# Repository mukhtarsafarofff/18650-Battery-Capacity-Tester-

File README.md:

(ENG)  Nowadays it is difficult to know the capacity retained in 18650 batteries and when we are buying , it is really difficult to distinguish between a real and fake battery .The whole schematic is divided into to followings sections:
1. Constant Current Load Circuit
2. Battery Voltage Measurement Circuit
3. User Interface Circuit
4. Buzzer Circuit

The power supply circuit consists of a DC Jack ( 7-9V) and two filter capacitors C1 and C2. The power output (Vin) is connected to the Arduino pin Vin. Here I am using the Arduino on-board voltage regulator to step down the voltage to 5V.
The main component of constant current load circuit is LM358 IC.LM358 is a dual amplifier in a single package.
This op-amp, R3, and the MOSFET build a constant current load circuit. When we set the voltage on the non-inverting input pin, the op-amp turns on the MOSFET and tries to get the same voltage across the R3. The Voltage appears due to the ohms law, as current flows through the resistor a voltage drop must appear. So I can control the current through the load resistor (R4) by changing the PWM signal pulse width.
The battery voltage is measured by the Arduino analog input pin A0. Two capacitors C1 and C2 are used to filter out the noises coming from the constant current load circuit which can degrade the ADC conversion performance.The user interface circuit consists of two push buttons and a 0.96" I2C OLED display. The Up and Down push-button is to increase or decrease the PWM pulse width. R3 and R4 are pull-up resistors for the Up and Down push-buttons. C7 and C8 are used to debounce the push buttons. The third push-button (RST) is used for resetting the Arduino.The buzzer circuit is used to alert the starting and end of the test. A 5V buzzer is hooked to Arduino digital pin D9.The theory is based on the voltage comparison of the inverting (pin-2) and the non-inverting (pin-3) inputs of the OpAmp.When I set the voltage applied to the non-inverting input by adjusting the PWM signal, the output of the opamp opens the gate of MOSFET. As the MOSFET turn-on, the current runs through R1, it creates a voltage drop, which provides negative feedback to OpAmp. It controls the MOSFET in such a way that the voltages at its inverting and non-inverting inputs are equal.The PWM signal from the Arduino is filtered by using a low pass filter circuit ( R2 and C1).To calculate battery capacity i use this formule : Battery Capacity (mAh) = Current ( I ) in mA x Time (T ) in Hours
The discharge current can be adjusted by pressing the Up and Down Button. The time duration is measured by using a timer in the Arduino code.

(DEU)  Heutzutage ist es schwierig zu wissen, welche Kapazität in 18650-Batterien erhalten ist, und wenn wir kaufen, ist es wirklich schwer, zwischen einer echten und einer gefälschten Batterie zu unterscheiden. Das gesamte Schaltbild ist in folgende Abschnitte unterteilt:
1)Konstantstromlastschaltung
2)Batteriespannungsmesskreis
3)Benutzerschnittstellenkreis
4)Summer-Schaltung

Die Stromversorgungsschaltung besteht aus einer Gleichstrombuchse (7-9V) und zwei Filterkondensatoren C1 und C2. Die Leistungsausgabe (Vin) ist mit dem Arduino-Pin Vin verbunden. Hier verwende ich den eingebauten Spannungsregler des Arduino, um die Spannung auf 5V zu reduzieren. Die Hauptkomponente der Konstantstromlastschaltung ist der LM358-IC. LM358 ist ein Doppelverstärker in einem einzigen Gehäuse.Dieser Operationsverstärker, R3 und der MOSFET bilden eine Konstantstromlastschaltung.Wenn wir die Spannung am nicht invertierenden Eingangspin einstellen, schaltet der Operationsverstärker den MOSFET ein und versucht, die gleiche Spannung über dem R3 zu erhalten.Die Spannung entsteht aufgrund des Ohmschen Gesetzes, da der Strom durch den Widerstand fließt, muss ein Spannungsabfall auftreten.So kann ich den Strom durch den Lastwiderstand (R4) steuern, indem ich die Pulsbreite des PWM-Signals ändere.Die Batteriespannung wird vom Arduino-Analogeingangspin A0 gemessen.Zwei Kondensatoren C1 und C2 werden verwendet, um die Störungen herauszufiltern, die von der Konstantstromlastschaltung kommen, welche die ADC-Konvertierungsleistung beeinträchtigen können. Die Benutzerschnittstellenschaltung besteht aus zwei Drucktasten und einem 0,96" I2C-OLED-Display. Die "Auf" und "Ab" Drucktasten dienen dazu, die PWM-Pulsbreite zu erhöhen oder zu verringern. R3 und R4 sind Pull-Up-Widerstände für die "Auf" und "Ab" Drucktasten. C7 und C8 dienen zur Entprellung der Drucktasten. Die dritte Drucktaste (RST) wird zum Zurücksetzen des Arduino verwendet. Die Summer-Schaltung wird verwendet, um den Beginn und das Ende des Tests anzuzeigen. Ein 5V-Summer ist mit dem Arduino-Digitalpin D9 verbunden. Die Theorie basiert auf dem Spannungsvergleich der invertierenden (Pin-2) und nicht invertierenden (Pin-3) Eingänge des Operationsverstärkers. Wenn ich die am nicht invertierenden Eingang angewandte Spannung durch Anpassen des PWM-Signals einstelle, öffnet der Ausgang des Operationsverstärkers das Gate des MOSFETs.Wenn der MOSFET eingeschaltet wird, fließt der Strom durch R1, es entsteht ein Spannungsabfall, der dem Operationsverstärker eine negative Rückkopplung liefert. Er steuert den MOSFET so, dass die Spannungen an seinen invertierenden und nicht invertierenden Eingängen gleich sind. Das PWM-Signal vom Arduino wird durch Verwendung einer Tiefpassfilterschaltung (R2 und C1) gefiltert.Um die Batteriekapazität zu berechnen, verwende ich diese Formel: Batteriekapazität (mAh) = Strom (I) in mA x Zeit (T) in Stunden. Der Entladestrom kann durch Drücken der "Auf" und "Ab" Tasten eingestellt werden. Die Zeitdauer wird durch Verwendung eines Timers im Arduino-Code gemessen.

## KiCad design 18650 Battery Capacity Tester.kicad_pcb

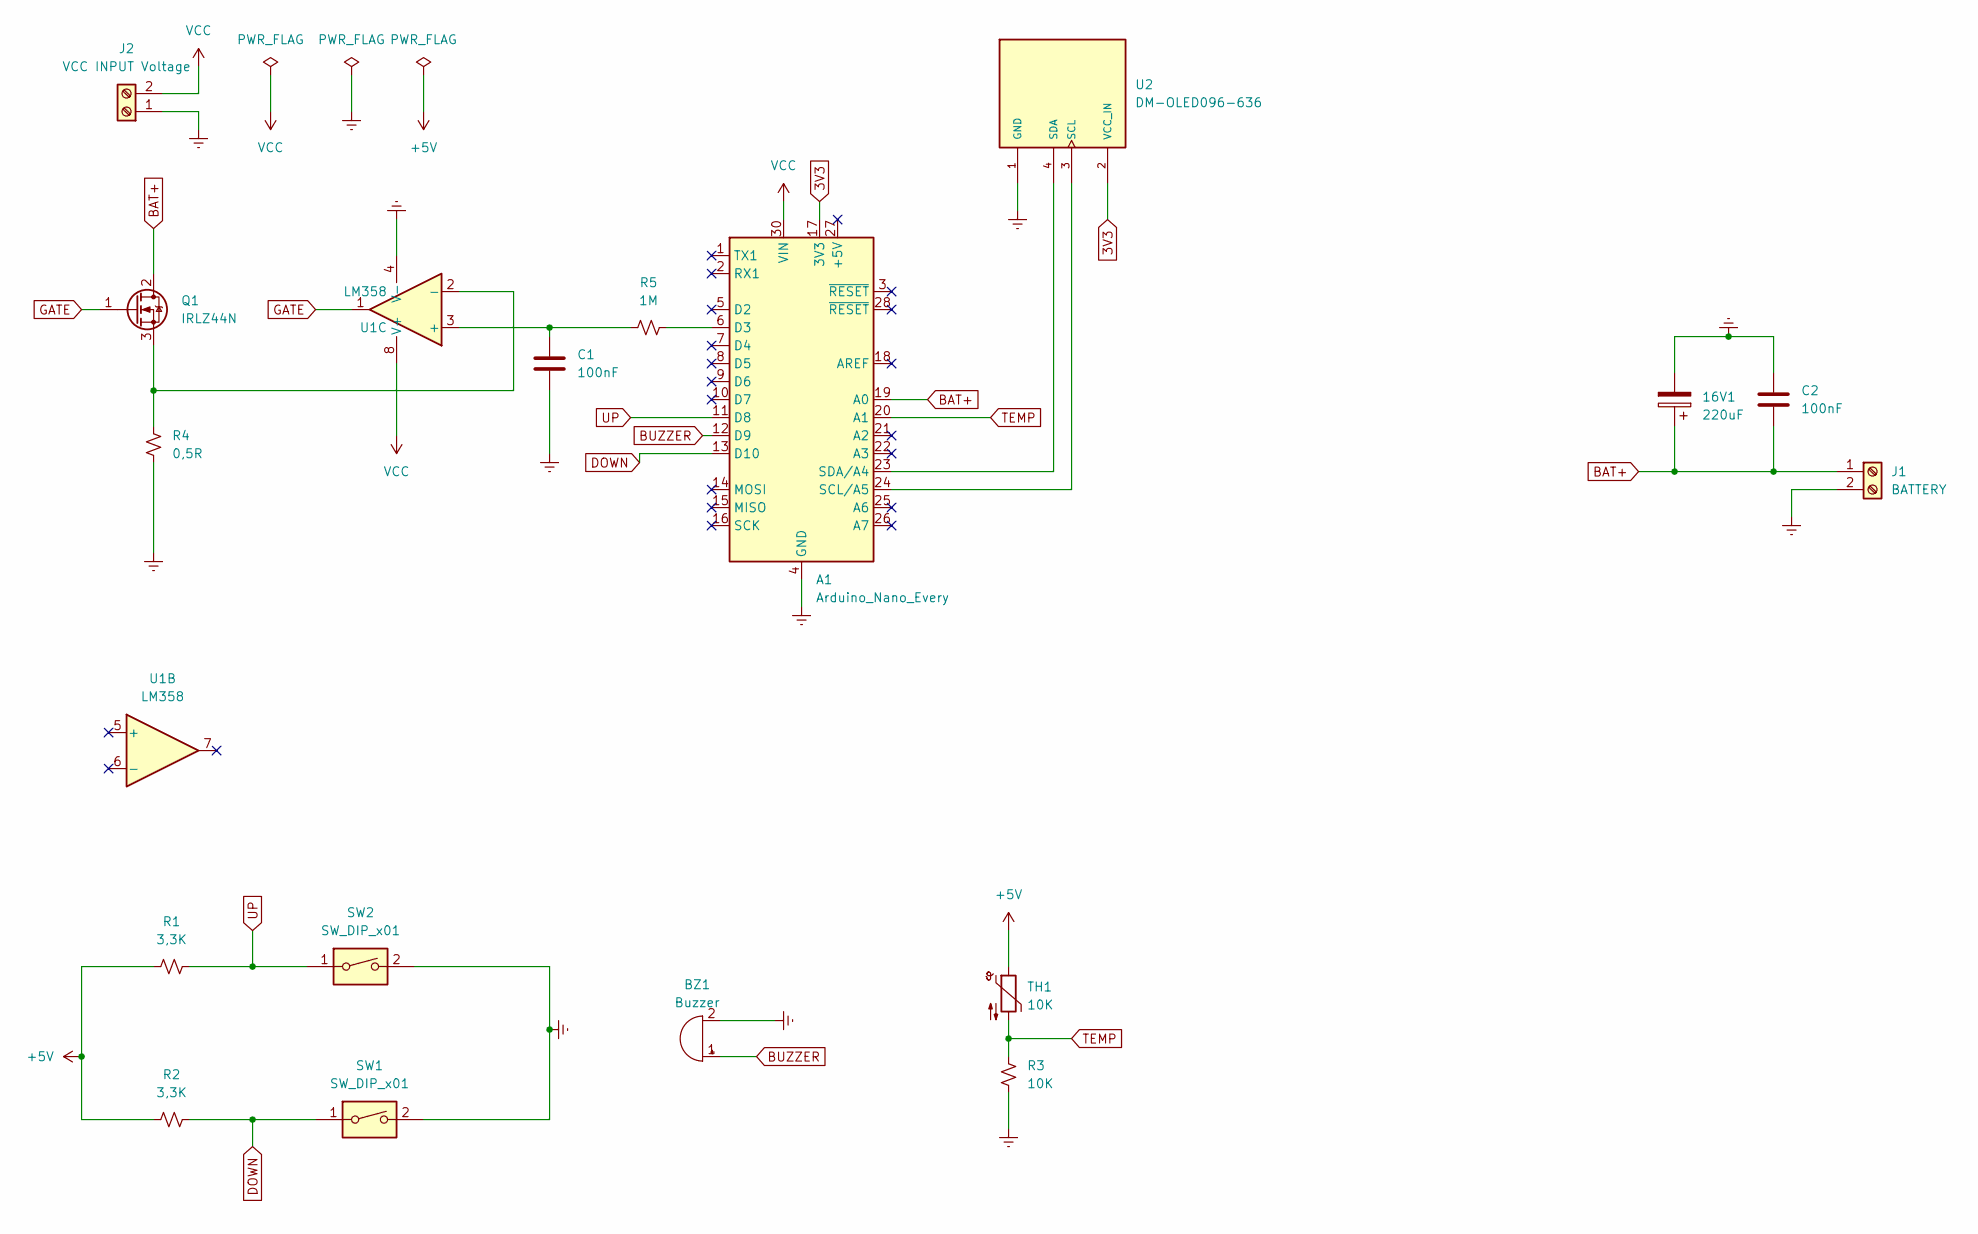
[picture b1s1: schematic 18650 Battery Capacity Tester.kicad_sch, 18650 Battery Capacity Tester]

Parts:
16V1: 220uF; CP_Radial_D10.0mm_P7.50mm
A1: Arduino_Nano_Every; Arduino_Nano
BZ1: Buzzer; Buzzer_15x7.5RM7.6
C1, C2: 100nF; C_Disc_D8.0mm_W5.0mm_P10.00mm
J1: BATTERY; TerminalBlock_bornier-2_P5.08mm
J2: VCC INPUT Voltage; TerminalBlock_bornier-2_P5.08mm
Q1: IRLZ44N; TO-220-3_Vertical
R1, R2: 3,3K; R_Axial_DIN0309_L9.0mm_D3.2mm_P12.70mm_Horizontal
R3: 10K; R_Axial_DIN0309_L9.0mm_D3.2mm_P12.70mm_Horizontal
R4: 0,5R; R_Axial_DIN0309_L9.0mm_D3.2mm_P12.70mm_Horizontal
R5: 1M; R_Axial_DIN0309_L9.0mm_D3.2mm_P12.70mm_Horizontal
SW1, SW2: SW_DIP_x01; SW_CW_GPTS203211B
TH1: 10K; R_Axial_DIN0411_L9.9mm_D3.6mm_P7.62mm_Vertical
U1: LM358; DIP-8_W7.62mm
U2: DM-OLED096-636; MODULE_DM-OLED096-636; PARTREV 2018-09-10

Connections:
3V3: A1.17 (3V3), U2.2 (VCC_IN)
+5V: R1.1, R2.1, TH1.1
BAT+: 16V1.1, A1.19 (A0), C2.2, J1.1, Q1.2 (D)
BUZZER: A1.12 (D9), BZ1.1 (-)
DOWN: A1.13 (D10), R2.2, SW1.1
Earth: 16V1.2, A1.4 (GND), A1.29 (GND), BZ1.2 (+), C1.2, C2.1, J1.2, J2.1, R3.1, R4.1, SW1.2, SW2.2, U1.4 (V-), U2.1 (GND)
GATE: Q1.1 (G), U1.1
unnamed: A1.6 (D3), R5.1
unnamed: A1.24 (SCL/A5), U2.3 (SCL)
unnamed: A1.23 (SDA/A4), U2.4 (SDA)
unnamed: Q1.3 (S), R4.2, U1.2 (-)
unnamed: C1.1, R5.2, U1.3 (+)
TEMP: A1.20 (A1), R3.2, TH1.2
UP: A1.11 (D8), R1.2, SW2.1
VCC: A1.30 (VIN), J2.2, U1.8 (V+)

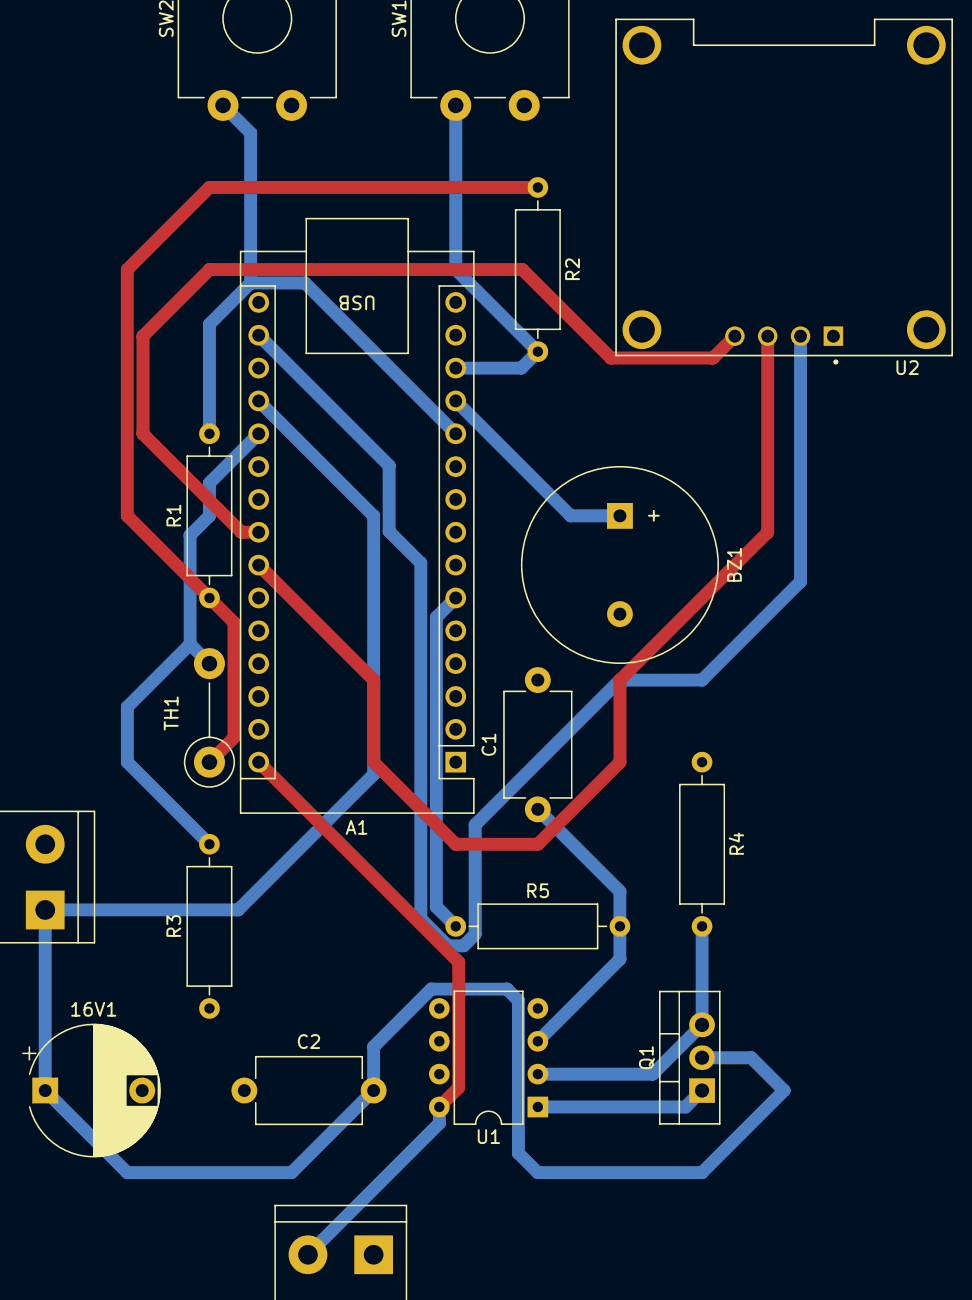
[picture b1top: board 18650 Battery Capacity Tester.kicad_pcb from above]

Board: 2 copper layers, 18 parts (0 on the bottom side), 15 nets.

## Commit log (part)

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2024-03-31 18650 Battery Capacity tester is accomplished
2024-03-31 Create Nano Code for Battery Capacity Tester
